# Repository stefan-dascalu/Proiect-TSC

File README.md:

Dascalu Stefan-Nicolae 331CA
# Proiect-TSC
## Implementare:

- **Implementarea Schemei Electrice:**
  - Am implementat schema electrica exact conform modelului primit.
  - Am efectuat o **verificare a regulilor electrice (ERC)**; desi am intampinat cateva avertismente, le-am revizuit si considerat necritice.

- **Designul PCB:**
  - Dupa finalizarea schemei, am incarcat designul in mediul PCB.
  - Toate componentele au fost amplasate pe **TOP layer** conform ghidurilor de layout.
  - Pentru a asigura **proper grounding** si **signal integrity**, am creat un **GND plane** atat pe TOP layer, cat si pe BOTTOM layer.
  - Am verificat toate constrangerile de design, iar rutarea a fost finalizata cu o rata de succes de 99,6%.
  - In timpul designului PCB, am intampinat si rezolvat erori de tip "airwire unrouted".

- **Fisiere de Productie:**
  - Am generat fisierele **Gerber**, **Pick and Place** si **BOM**.

- **Modelul 3D:**
  - Modelul 3D al dispozitivului a fost implementat.

## Imagine 3D

## Diagrama bloc a proiectului:

## Descriere Hardware si Asignarea Pinilor pe ESP32-C6

- **ESP32-C6-WROOM-1-N8 (Microcontroler Principal)**
  - Microcontrolerul ofera suport pentru WiFi 6, Bluetooth 5 LE si dispune de un nucleu RISC-V ce functioneaza pana la 160 MHz.
  - Interfetele disponibile includ SPI, I2C, UART si GPIO, fiind baza pentru conectarea celorlalte module.

- **BME688 (Senzor Ambiental)**
  - Maseaza temperatura, umiditatea, presiunea atmosferica si calitatea aerului.
  - Interfata: I2C
  - Pini utilizati: SDA -> IO21, SCL -> IO22
  - Alegerea acestor pini se face pentru a beneficia de o comunicatie I2C rapida si fiabila.

- **DS3231SN (Real-Time Clock)**
  - Asigura cronometrare de inalta precizie, chiar si in lipsa alimentarii principale.
  - Interfata: I2C (se partajeaza cu BME688)
  - Pini utilizati: SCL -> IO22, SDA -> IO21, INT_RTC -> IO8, 32KHZ -> IO1, RTC_RST -> IO18
  - Acesti pini asigura functii suplimentare de intrerupere si reset pentru modulul RTC.

- **Afisaj E-Ink (7.5 inch)**
  - Afisajul ofera o rezolutie de 800 x 480 pixeli si functioneaza prin interfata SPI.
  - Pini utilizati: EPD_CS -> IO10, EPD_DC -> IO5, EPD_RST -> IO23, EPD_BUSY -> IO3 (EPD_BUSY este partajat cu MISO)
  - Linile MOSI si SCK sunt partajate cu modulul SD, permitand optimizarea numarului de pini utilizati.

- **Modul SD Card**
  - Permite stocarea locala a datelor, cum ar fi e-bookurile sau firmware-ul.
  - Interfata: SPI
  - Pini utilizati: SS_SD -> IO4, MOSI -> IO7, MISO -> IO2, SCK -> IO6
  - Aceste asignari asigura sincronizarea corecta a datelor pe interfata SPI.

- **Memorie Externa Flash (W25Q512JVEIQ, 64MB)**
  - Memoria flash externa este utilizata pentru stocarea firmware-ului si a datelor importante.
  - Interfata: SPI
  - Pini utilizati: FLASH_CS -> IO12 (MOSI, MISO si SCK sunt partajate cu modulul SD)
  
- **Interfata USB/SD**
  - Asigura alimentarea si transferul de date prin USB.
  - Pini utilizati: USB_D+ -> IO13, USB_D- -> IO12

- **Butoane Boot si Reset**
  - Permit accesul la modul boot si efectuarea unui reset hardware.
  - Pini utilizati: IO/BOOT -> IO9, RESET -> un pin dedicat (conform schemei)

- **Sistem de Alimentare si Management**
  - Bateria Li-Po (3.7V, 2500mAh) alimenteaza sistemul.
  - Controlerul de incarcare MCP73831 gestioneaza incarcarea prin USB-C.
  - Monitorizarea bateriei se realizeaza cu MAX17048, care comunica prin I2C (reutilizand SDA/IO21 si SCL/IO22).
  - Regulatorul LDO XC6220A331MR-G furnizeaza 3.3V stabile pentru toate modulele.
  
- **Conector USB-C**
  - Principalul conector pentru alimentare si transfer de date, protejat de circuit ESD.

- **Conector Qwiic/Stemma QT**
  - Permite extinderea usoara a sistemului cu module suplimentare I2C.
  - Utilizeaza acelasi bus I2C (SDA -> IO21, SCL -> IO22) ca si senzorii si modulul RTC.

## BOM:
| Component                                               | Link             |
|---------------------------------------------------------|------------------|
| ADAFRUIT_LEDCHIP-LED0603                                  | [Click here](https://www.snapeda.com/parts/KP-1608SURCK/Kingbright/view-part/?ref=search&t=LED%200603)   |
| SJ                                                      | [Click here](https://grabcad.com/library/solder-jumpers-1)   |
| 112ATAARR03                       | [Click here](https://www.snapeda.com/parts/112A-TAAR-R03/Attend/view-part/)   |
| RCL_CPOL-EUCT3528                                       | [Click here](https://grabcad.com/library/tantalum-smd-capacitor-type-b-3528-1)   |
| BUTTON_CUSYOMV1                                         | [Click here](https://www.snapeda.com/search/?q=EVQP7L01P&search-type=parts)   |
| DS3231SN#                                              | [Click here](https://www.snapeda.com/parts/DS3231SN%23/Analog%20Devices/view-part/?ref=search&t=DS3231SN%23)   |
| ESP32-C6-WROOM-1-N8                                     | [Click here](https://www.snapeda.com/parts/ESP32-C6-WROOM-1-N8/Espressif%20Systems/view-part/?ref=search&t=ESP32-C6-WROOM-1-N8)   |
| 744043680                                 | [Click here](https://eu.mouser.com/ProductDetail/Wurth-Elektronik/744043680?qs=PGXP4M47uW6VkZq%252BkzjrHA%3D%3D)   |
| BD5229G-TR                                  | [Click here](https://www.snapeda.com/parts/BD5229G-TR/Rohm/view-part/?ref=search&t=BD5229G-TR)   |
| ESP32_WROVER_BME680_BME680                               | [Click here](https://www.snapeda.com/parts/BME680/Bosch%20Sensortec/view-part/?ref=search&t=bme680)   |
| ESP32_WROVER_EAGLE-LTSPICE_R                              | [Click here](https://componentsearchengine.com/part-view/R0402%201%25%20100%20K%20(RC0402FR-07100KL)/YAGEO)   |
| ESP32_WROVER_SPARKFUN-DISCRETESEMI_MOSFET_PCH                                | [Click here](https://componentsearchengine.com/part-view/DMG2305UX-7/Diodes%20Incorporated)   |
| ESP32_WROVER_SPARKFUN-IC-POWER_MCP73831                              | [Click here](https://componentsearchengine.com/part-view/MCP73831T-2ACI%2FOT/Microchip)   |
| FH34SRJ-24S-0.5SH_99_                                 | [Click here](https://componentsearchengine.com/part-view/FH34SRJ-24S-0.5SH(99)/Hirose)   |
| TP                                 | - |
| SI1308EDL-T1-GE3                                  | [Click here](https://www.snapeda.com/parts/SI1308EDL-T1-GE3/Vishay/view-part/)   |
| ESP32_WROVER_AVX---SD0805S020S1R0_AVX_SD0805S020S1R0_0_0  | [Click here](https://componentsearchengine.com/part-view/SD0805S020S1R0/Kyocera%20AVX)   |
| CPH3225A                                               | [Click here](https://www.snapeda.com/parts/CPH3225A/Seiko/view-part/)   |
| MAX17048G+T10                                          | [Click here](https://www.snapeda.com/parts/MAX17048G+T10/Analog%20Devices/view-part/)   |
| MBR0530                                               | [Click here](https://www.snapeda.com/parts/MBR0530/Onsemi/view-part/)   |
| PGB1010603MR                                           | [Click here](https://www.snapeda.com/parts/PGB1010603MR/Littelfuse/view-part/)   |
| QWIIC_RIGHT_ANGLE (QWIIC_CONNECTORJS-1MM)               | [Click here](https://www.snapeda.com/parts/PRT-14417/SparkFun/view-part/)   |
| SAMACSYS_PARTS_USB4110-GF-A                              | [Click here](https://www.snapeda.com/parts/USB4110-GF-A./Global%20Connector%20Technology/view-part/)   |
| USBLC6-2SC6Y                                           | [Click here](https://www.snapeda.com/parts/USBLC6-2SC6Y/STMicroelectronics/view-part/?ref=dk&t=USBLC6-2SC6Y&con_ref=None)   |
| W25Q512JVEIQ                                           | [Click here](https://www.snapeda.com/parts/W25Q512JVEIQ/Winbond%20Electronics/view-part/?ref=search&t=W25Q512JVEIQ)   |
| XC6220A331MR-G                                         | [Click here](https://ro.mouser.com/ProductDetail/Torex-Semiconductor/XC6220A331MR-G?qs=AsjdqWjXhJ8ZSWznL1J0gg%3D%3D&utm_source=octopart&utm_medium=aggregator&utm_campaign=865-XC6220A331MR-G&utm_content=Torex%20Semiconductor)   |

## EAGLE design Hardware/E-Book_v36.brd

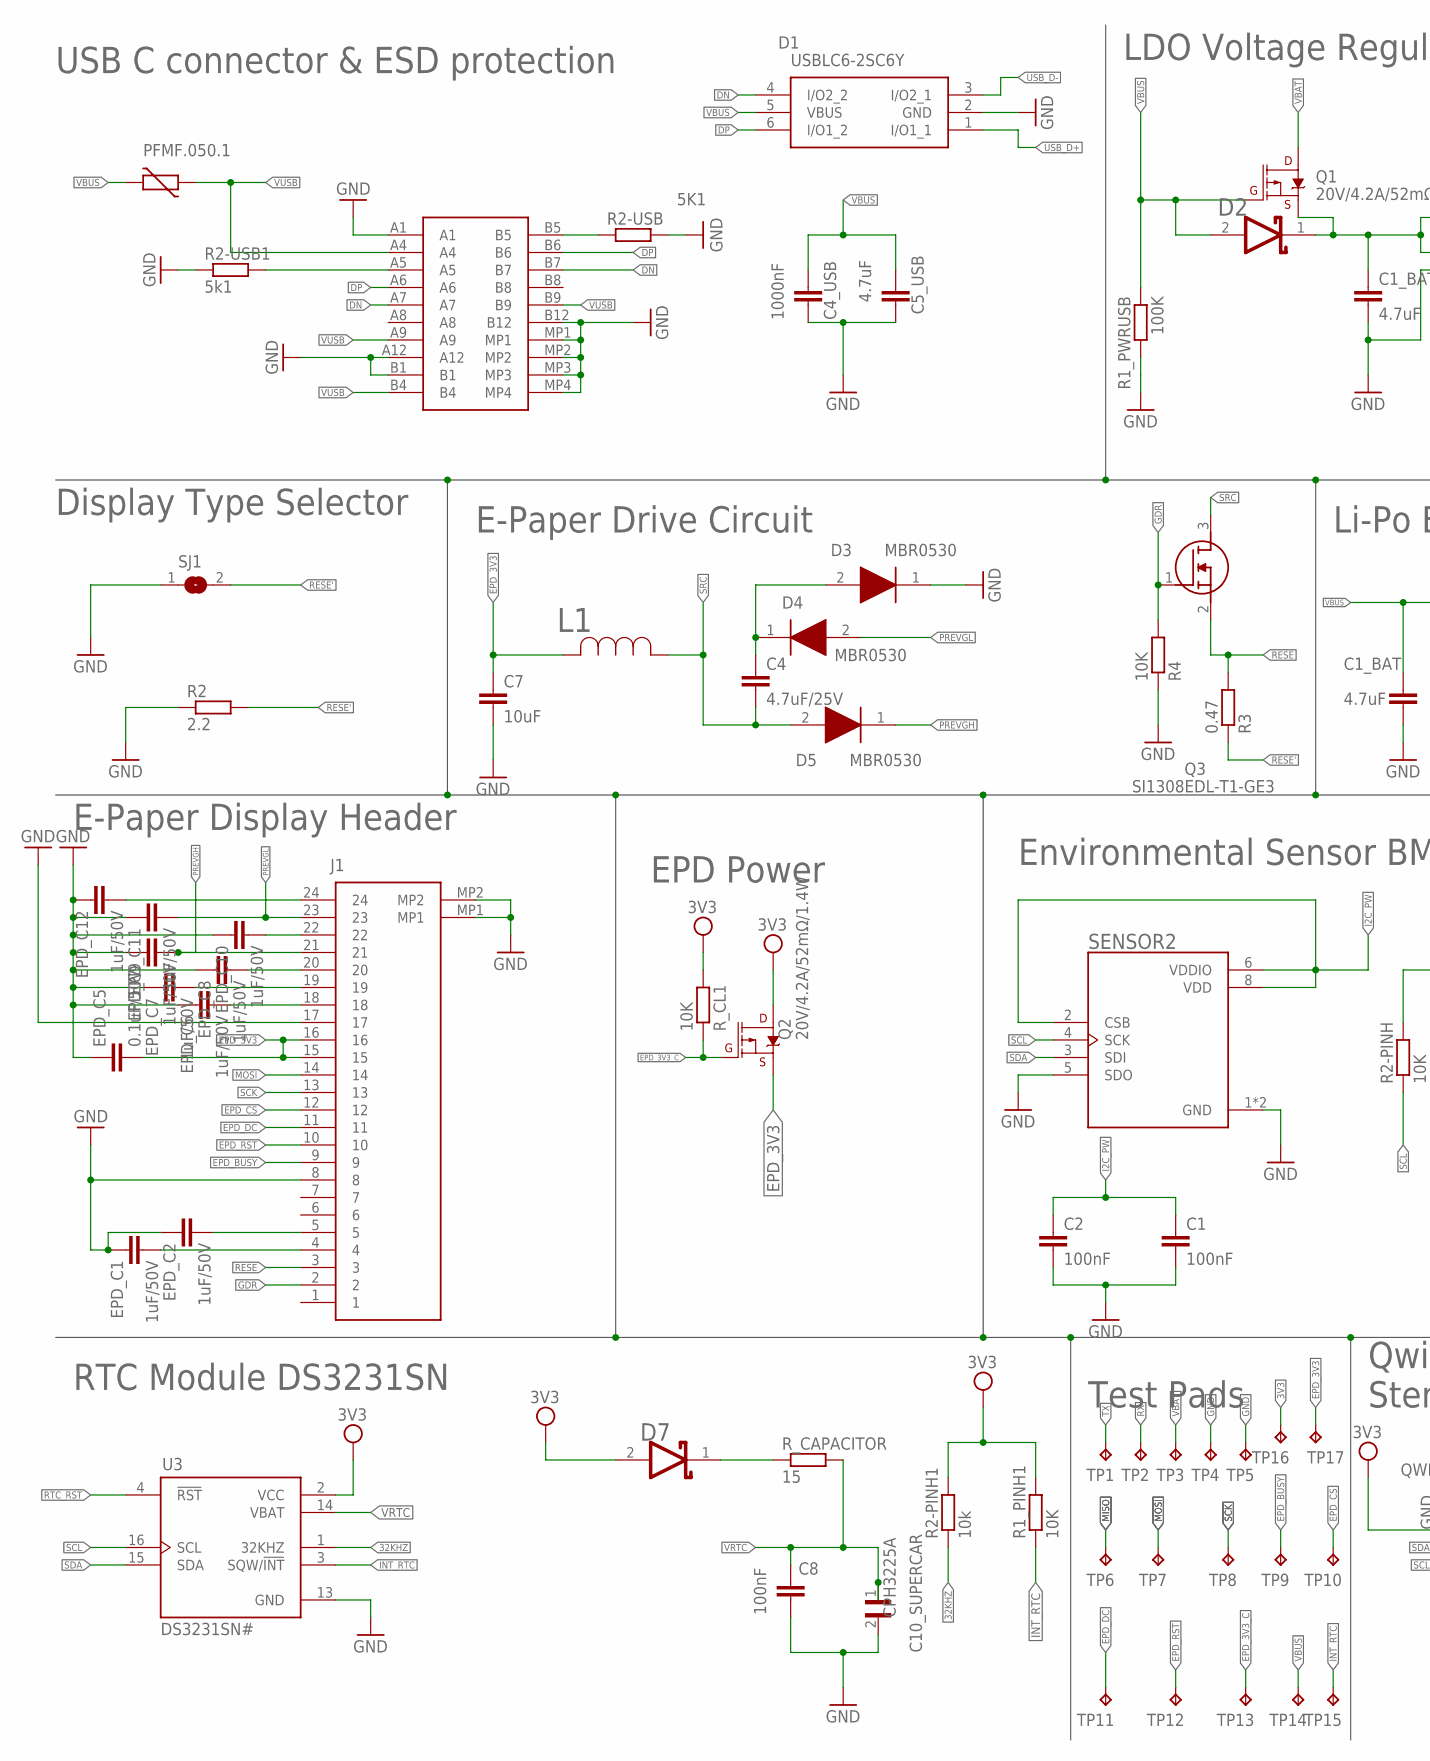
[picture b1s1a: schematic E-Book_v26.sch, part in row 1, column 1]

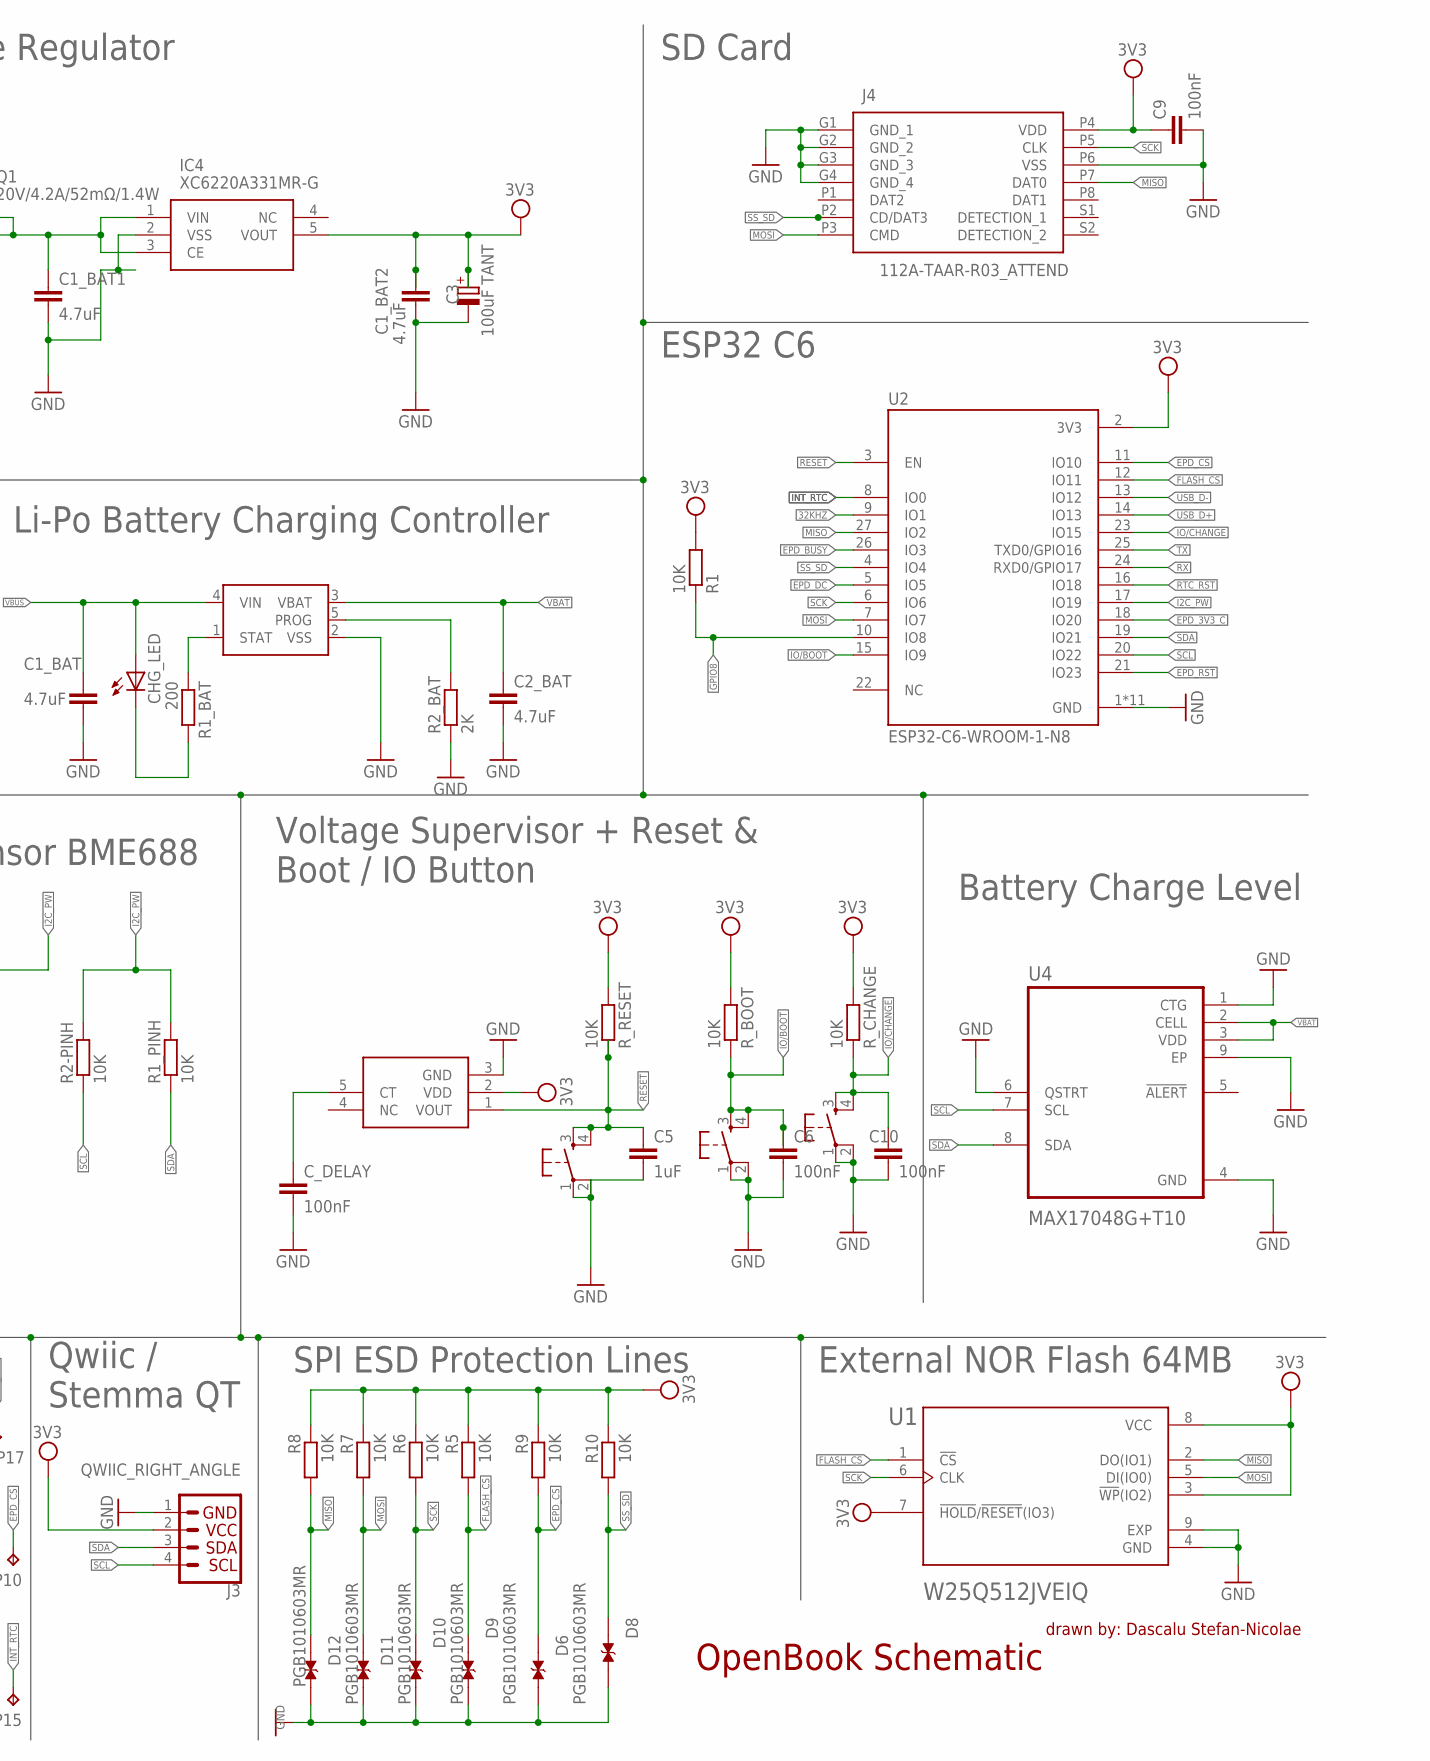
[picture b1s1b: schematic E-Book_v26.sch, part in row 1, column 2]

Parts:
C1, C2, C6, C8, C9, C10: 100nF; ESP32_WROVER_EAGLE-LTSPICE_C0402
C1_BAT, C2_BAT: 4.7uF; ESP32_WROVER_EAGLE-LTSPICE_C0402
C1_BAT1, C1_BAT2, C5_USB: 4.7uF; EAGLE-LTSPICE_C0402
C3: 100uF TANT; RCL_CT3528
C4: 4.7uF/25V; ESP32_WROVER_EAGLE-LTSPICE_C0402
C4_USB: 1000nF; EAGLE-LTSPICE_C0402
C5: 1uF; ESP32_WROVER_EAGLE-LTSPICE_C0402
C7: 10uF; ESP32_WROVER_EAGLE-LTSPICE_C0402
C10_SUPERCAR: CPH3225A; CAPCP3225X100N
CHG_LED: ADAFRUIT_LEDCHIP-LED0603; ADAFRUIT_CHIP-LED0603
C_DELAY: 100nF; ESP32_WROVER_EAGLE-LTSPICE_C0402
D1: USBLC6-2SC6Y; SOT95P280X145-6N
D2, D7: ESP32_WROVER_AVX---SD0805S020S1R0_AVX_SD0805S020S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; ESP32_WROVER_AVX---SD0805S020S1R0_AVX_SD0805S020S1R0_0
D3, D4, D5: MBR0530; SOD3716X135N
D6, D8, D9, D10, D11, D12: PGB1010603MR; DIOC1608X36N
EPD_C1, EPD_C2, EPD_C6, EPD_C7, EPD_C8, EPD_C9, EPD_C10, EPD_C11, EPD_C12: 1uF/50V; ESP32_WROVER_EAGLE-LTSPICE_C0402
EPD_C5: 0.1uF/50V; ESP32_WROVER_EAGLE-LTSPICE_C0402
IC1: BD5229G-TR; SOT95P280X125-5N
IC4: XC6220A331MR-G; SOT95P280X120-5N
J1: FH34SRJ-24S-0.5SH_99_; FH34SRJ24S05SH99
J2: SAMACSYS_PARTS_USB4110-GF-A; SAMACSYS_PARTS_USB4110GFA
J3: QWIIC_RIGHT_ANGLE; JST04_1MM_RA
J4: 112A-TAAR-R03_ATTEND; 112ATAARR03ATTEND
L1: 744043680IND_4828-WE-TPC_WRE; IND_4828-WE-TPC_WRE
MCP73831: ESP32_WROVER_SPARKFUN-IC-POWER_MCP73831; ESP32_WROVER_SPARKFUN-IC-POWER_SOT23-5
PFMF.050.1: ESP32C6_VARISTORCN1812; ESP32C6_VARISTOR_CT/CN1812
Q1, Q2: 20V/4.2A/52mΩ/1.4W; ESP32_WROVER_SPARKFUN-DISCRETESEMI_SOT23-3
Q3: SI1308EDL-T1-GE3; SOT65P210X110-3N
R1, R1_PINH, R1_PINH1, R2-PINH, R4, R5, R6, R7, R8, R9, R10: 10K; ESP32_WROVER_EAGLE-LTSPICE_R0402
R1_BAT: 200; ESP32_WROVER_EAGLE-LTSPICE_R0402
R1_PWRUSB: 100K; ESP32_WROVER_EAGLE-LTSPICE_R0402
R2: 2.2; ESP32_WROVER_EAGLE-LTSPICE_R0402
R2-PINH1: 10k; ESP32_WROVER_EAGLE-LTSPICE_R0402
R2-USB: 5K1; ESP32_WROVER_EAGLE-LTSPICE_R0402
R2-USB1: 5k1; ESP32_WROVER_EAGLE-LTSPICE_R0402
R2_BAT: 2K; ESP32_WROVER_EAGLE-LTSPICE_R0402
R3: 0.47; ESP32_WROVER_EAGLE-LTSPICE_R0402
RESET_BUTTON: BUTTON_CUSYOMV1; MYBUTTON
R_BOOT: 10K; ESP32_WROVER_EAGLE-LTSPICE_R0402
R_CAPACITOR: 15; ESP32_WROVER_EAGLE-LTSPICE_R0402
R_CHANGE: 10K; ESP32_WROVER_EAGLE-LTSPICE_R0402
R_CL1: 10K; ESP32_WROVER_EAGLE-LTSPICE_R0402
R_RESET: 10K; ESP32_WROVER_EAGLE-LTSPICE_R0402
SENSOR2: ESP32_WROVER_BME680_BME680; ESP32_WROVER_BME680_PSON80P300X300X100-8N
SJ1: SJ
TP1, TP2, TP3, TP4, TP5, TP6, TP7, TP8, TP9, TP10, TP11, TP12, TP13, TP14, TP15, TP16, TP17: TPTP20R; TP20R
U1: W25Q512JVEIQ; SON127P600X800X80-9N
U2: ESP32-C6-WROOM-1-N8; XCVR_ESP32-C6-WROOM-1-N8
U3: DS3231SN#; SOIC127P1032X265-16N
U4: MAX17048G+T10; SON50P200X200X80-9N
U$1, U$3: BUTTON_CUSYOMV1; MYBUTTON

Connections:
3V3: C1_BAT2.1, C3.+, C9.1, D7.2 (ANODE), IC1.2 (VDD), IC4.5 (VOUT), J3.2, J4.P4 (VDD), Q2.3 (D), R1.2, R1_PINH1.2, R2-PINH1.2, R5.1, R6.1, R7.1, R8.1, R9.1, R10.1, R_BOOT.2, R_CHANGE.2, R_CL1.2, R_RESET.2, TP16.TP, U1.3 (!WP!(IO2)), U1.7 (!HOLD!/!RESET!(IO3)), U1.8 (VCC), U2.2 (3V3), U3.2 (VCC)
32KHZ: R2-PINH1.1, U2.9 (IO1), U3.1 (32KHZ)
DN: D1.4 (I/O2_2), J2.A7, J2.B7
DP: D1.6 (I/O1_2), J2.A6, J2.B6
EPD_3V3: C7.1, EPD_C5.2, J1.15, J1.16, L1.2, Q2.2 (S), TP17.TP
EPD_3V3_C: Q2.1 (G), R_CL1.1, TP13.TP, U2.18 (IO20)
EPD_BUSY: J1.9, TP9.TP, U2.26 (IO3)
EPD_CS: D6.1, J1.12, R9.2, TP10.TP, U2.11 (IO10)
EPD_DC: J1.11, TP11.TP, U2.5 (IO5)
EPD_RST: J1.10, TP12.TP, U2.21 (IO23)
FLASH_CS: D9.1, R5.2, U1.1 (!CS), U2.12 (IO11)
GDR: J1.2, Q3.1 (G), R4.2
GND: C1.2, C1_BAT.2, C1_BAT1.2, C1_BAT2.2, C2.2, C2_BAT.2, C3.-, C4_USB.2, C5.2, C5_USB.2, C6.2, C7.2, C8.2, C9.2, C10.2, C10_SUPERCAR.2, C_DELAY.2, D1.2 (GND), D3.1 (K), D6.2, D8.2, D9.2, D10.2, D11.2, D12.2, EPD_C1.1, EPD_C2.1, EPD_C5.1, EPD_C6.1, EPD_C7.1, EPD_C8.1, EPD_C9.1, EPD_C10.1, EPD_C11.1, EPD_C12.1, IC1.3 (GND), IC4.2 (VSS), J1.8, J1.17, J1.MP1, J1.MP2, J2.A1, J2.A12, J2.B1, J2.B12, J2.MP1, J2.MP2, J2.MP3, J2.MP4, J3.1, J4.G1 (GND_1), J4.G2 (GND_2), J4.G3 (GND_3), J4.G4 (GND_4), J4.P6 (VSS), MCP73831.2 (VSS), R1_PWRUSB.2, R2.1, R2-USB.2, R2-USB1.1, R2_BAT.1, R4.1, RESET_BUTTON.1, RESET_BUTTON.2, SENSOR2.1 (GND), SENSOR2.5 (SDO), SENSOR2.7 (GND), SJ1.1, TP4.TP, TP5.TP, U1.4 (GND), U1.9 (EXP), U2.1 (GND), U2.28 (GND), U2.29_1 (GND), U2.29_2 (GND), U2.29_3 (GND), U2.29_4 (GND), U2.29_5 (GND), U2.29_6 (GND), U2.29_7 (GND), U2.29_8 (GND), U2.29_9 (GND), U3.13 (GND), U4.1 (CTG), U4.4 (GND), U4.6 (QSTRT), U4.9 (EP), U$1.1, U$1.2, U$3.1, U$3.2
GPIO8: R1.1, U2.10 (IO8)
I2C_PW: C1.1, C2.1, R1_PINH.2, R2-PINH.2, SENSOR2.2 (CSB), SENSOR2.6 (VDDIO), SENSOR2.8 (VDD), U2.17 (IO19)
INT_RTC: R1_PINH1.1, TP15.TP, U2.8 (IO0), U3.3 (SQW/!INT)
IO/BOOT: C6.1, R_BOOT.1, U2.15 (IO9), U$3.3, U$3.4
IO/CHANGE: C10.1, R_CHANGE.1, U2.23 (IO15), U$1.3, U$1.4
MISO: D12.1, J4.P7 (DAT0), R8.2, TP6.TP, U1.2 (DO(IO1)), U2.27 (IO2)
MOSI: D11.1, J1.14, J4.P3 (CMD), R7.2, TP7.TP, U1.5 (DI(IO0)), U2.7 (IO7)
unnamed: J2.B5, R2-USB.1
unnamed: J2.A5, R2-USB1.2
unnamed: CHG_LED.C, R1_BAT.2
unnamed: EPD_C1.2, J1.4
unnamed: MCP73831.5 (PROG), R2_BAT.2
unnamed: EPD_C2.2, J1.5
unnamed: MCP73831.1 (STAT), R1_BAT.1
unnamed: EPD_C6.2, J1.18
unnamed: EPD_C7.2, J1.19
unnamed: EPD_C8.2, J1.20
unnamed: EPD_C10.2, J1.22
unnamed: EPD_C12.2, J1.24
unnamed: C_DELAY.1, IC1.5 (CT)
unnamed: C1_BAT1.1, D2.1 (CATHODE), IC4.1 (VIN), IC4.3 (CE), Q1.2 (S)
unnamed: C4.1, D3.2 (A), D4.1 (K)
unnamed: D7.1 (CATHODE), R_CAPACITOR.1
PREVGH: D5.1 (K), EPD_C9.2, J1.21
PREVGL: D4.2 (A), EPD_C11.2, J1.23
RESE: J1.3, Q3.2 (S), R3.2
RESE': R2.2, R3.1, SJ1.2
RESET: C5.1, IC1.1 (VOUT), RESET_BUTTON.3, RESET_BUTTON.4, R_RESET.1, U2.3 (EN)
RTC_RST: U2.16 (IO18), U3.4 (!RST)
RX: TP2.TP, U2.24 (RXD0/GPIO17)
SCK: D10.1, J1.13, J4.P5 (CLK), R6.2, TP8.TP, U1.6 (CLK), U2.6 (IO6)
SCL: J3.4, R2-PINH.1, SENSOR2.4 (SCK), U2.20 (IO22), U3.16 (SCL), U4.7 (SCL)
SDA: J3.3, R1_PINH.1, SENSOR2.3 (SDI), U2.19 (IO21), U3.15 (SDA), U4.8 (SDA)
SRC: C4.2, D5.2 (A), L1.1, Q3.3 (D)
SS_SD: D8.1, J4.P2 (CD/DAT3), R10.2, U2.4 (IO4)
TX: TP1.TP, U2.25 (TXD0/GPIO16)
USB_D+: D1.1 (I/O1_1), U2.14 (IO13)
USB_D-: D1.3 (I/O2_1), U2.13 (IO12)
VBAT: C2_BAT.1, MCP73831.3 (VBAT), Q1.3 (D), TP3.TP, U4.2 (CELL), U4.3 (VDD)
VBUS: C1_BAT.1, C4_USB.1, C5_USB.1, CHG_LED.A, D1.5 (VBUS), D2.2 (ANODE), MCP73831.4 (VIN), PFMF.050.1.2, Q1.1 (G), R1_PWRUSB.1, TP14.TP
VRTC: C8.1, C10_SUPERCAR.1, R_CAPACITOR.2, U3.14 (VBAT)
VUSB: J2.A4, J2.A9, J2.B4, J2.B9, PFMF.050.1.1

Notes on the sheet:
USB C connector & ESD protection
Display Type Selector
Test Pads
Qwiic / Stemma QT
External NOR Flash 64MB
drawn by: Dascalu Stefan-Nicolae
Battery Charge Level
OpenBook Schematic
EPD Power
Environmental Sensor BME688
SD Card
ESP32 C6
Li-Po Battery Charging Controller
E-Paper Display Header
SPI ESD Protection Lines
LDO Voltage Regulator
Voltage Supervisor + Reset & Boot / IO Button
E-Paper Drive Circuit
RTC Module DS3231SN

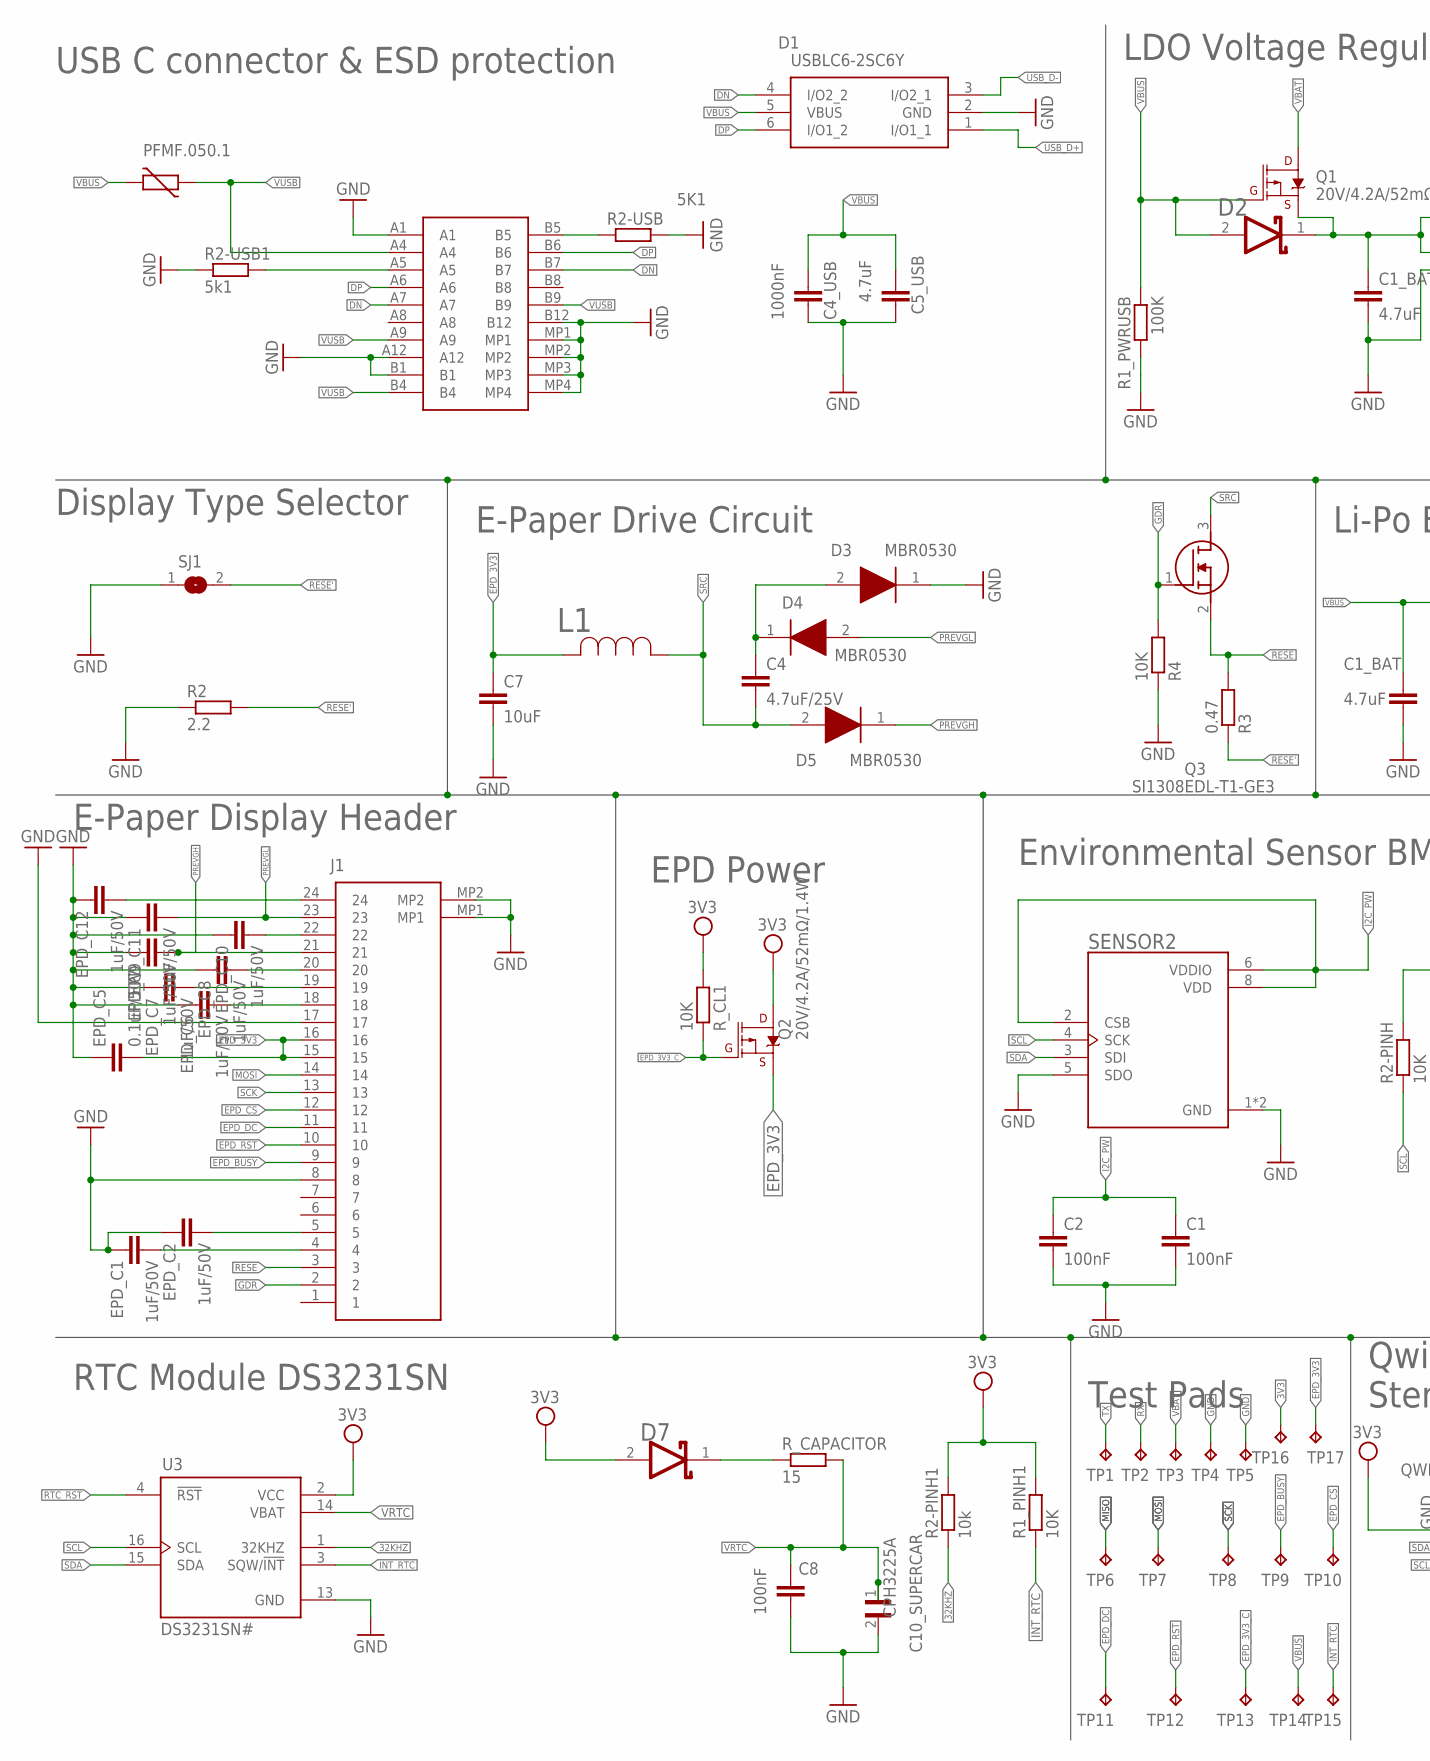
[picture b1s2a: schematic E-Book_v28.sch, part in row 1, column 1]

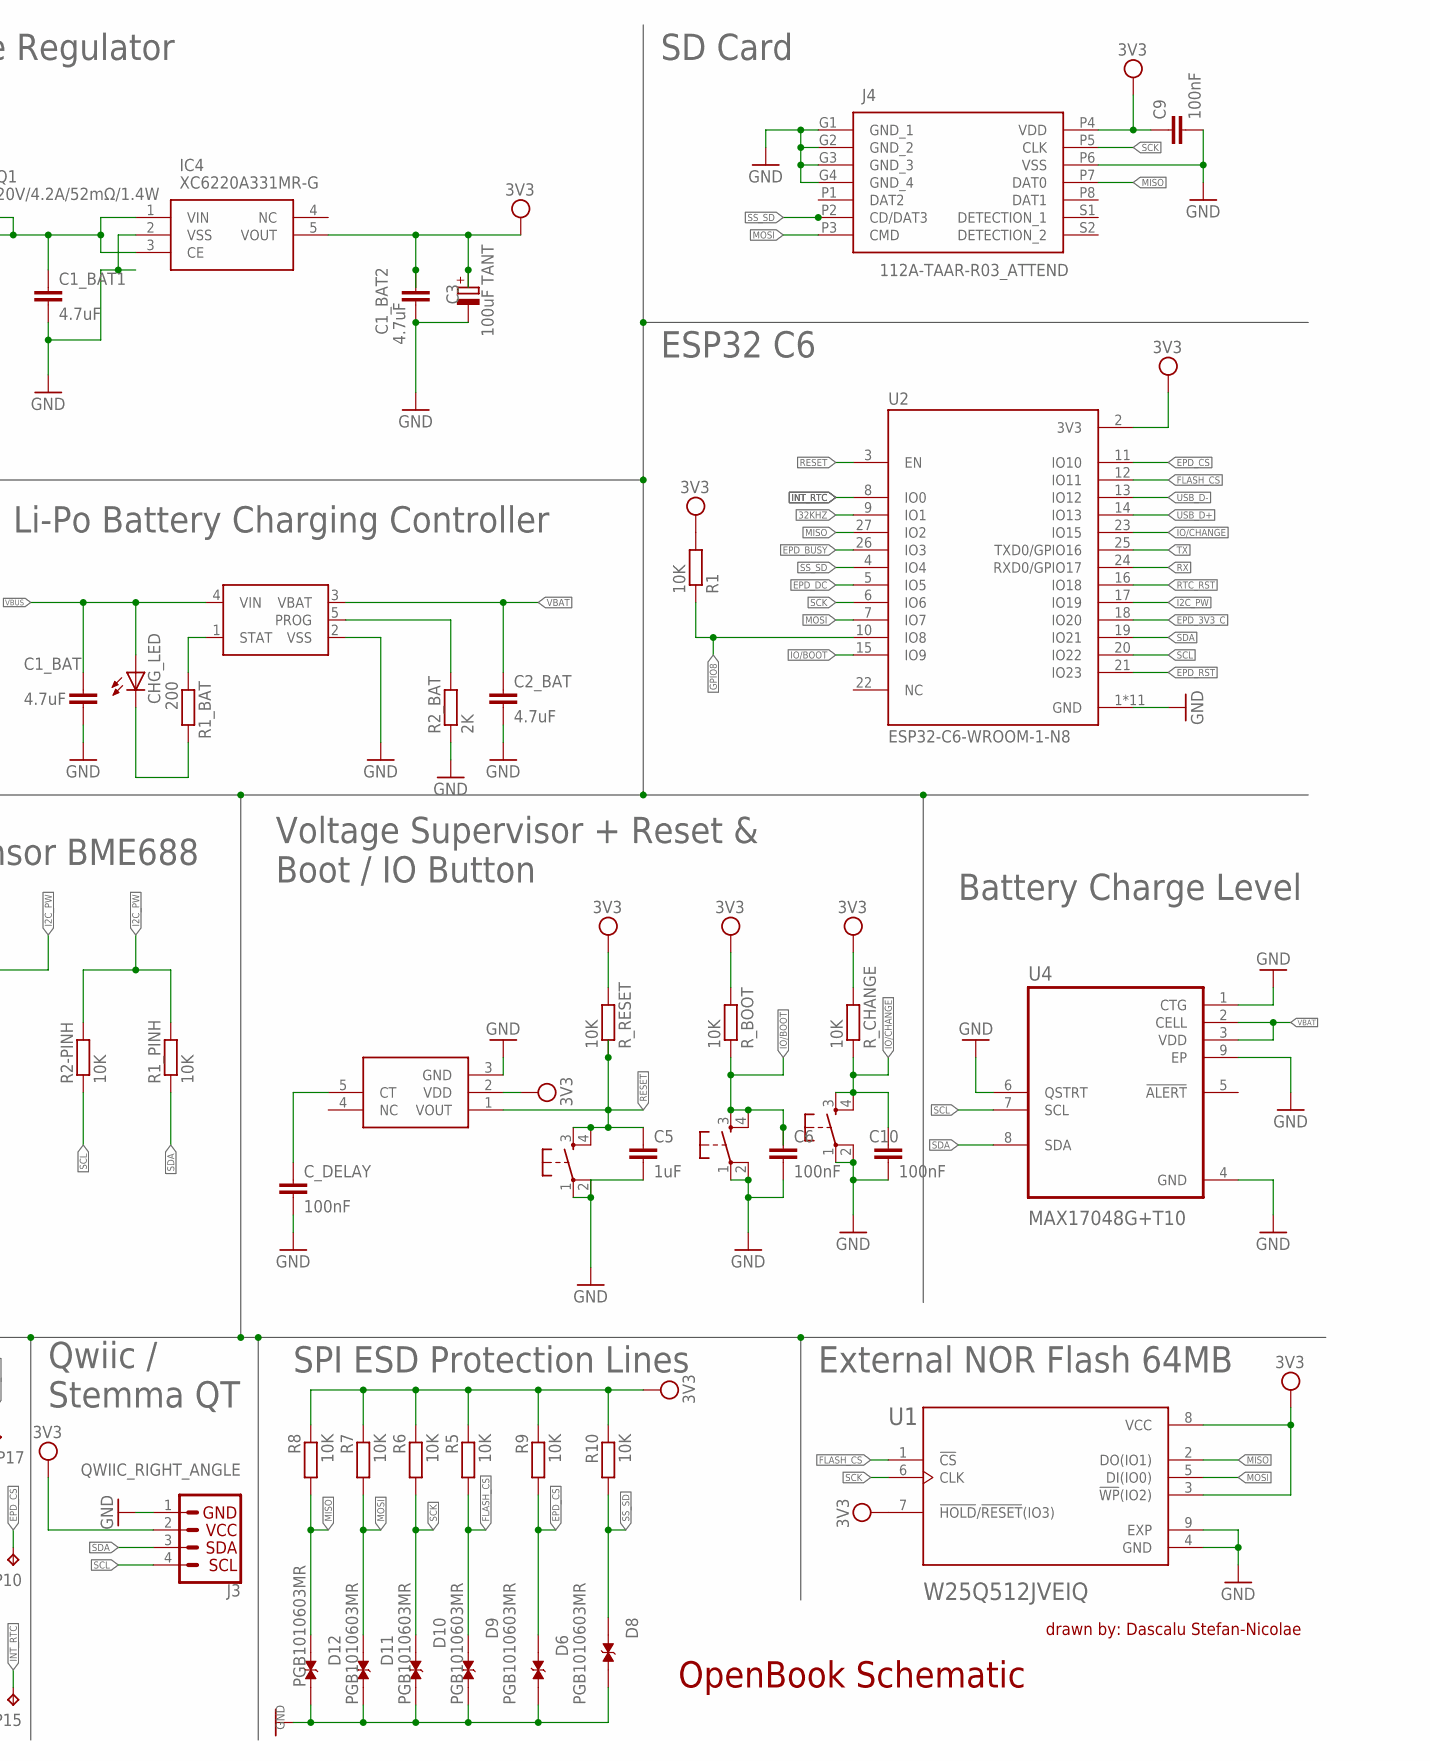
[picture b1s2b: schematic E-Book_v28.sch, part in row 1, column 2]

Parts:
C1, C2, C6, C8, C9, C10: 100nF; ESP32_WROVER_EAGLE-LTSPICE_C0402
C1_BAT, C2_BAT: 4.7uF; ESP32_WROVER_EAGLE-LTSPICE_C0402
C1_BAT1, C1_BAT2, C5_USB: 4.7uF; EAGLE-LTSPICE_C0402
C3: 100uF TANT; RCL_CT3528
C4: 4.7uF/25V; ESP32_WROVER_EAGLE-LTSPICE_C0402
C4_USB: 1000nF; EAGLE-LTSPICE_C0402
C5: 1uF; ESP32_WROVER_EAGLE-LTSPICE_C0402
C7: 10uF; ESP32_WROVER_EAGLE-LTSPICE_C0402
C10_SUPERCAR: CPH3225A; CAPCP3225X100N
CHG_LED: ADAFRUIT_LEDCHIP-LED0603; ADAFRUIT_CHIP-LED0603
C_DELAY: 100nF; ESP32_WROVER_EAGLE-LTSPICE_C0402
D1: USBLC6-2SC6Y; SOT95P280X145-6N
D2, D7: ESP32_WROVER_AVX---SD0805S020S1R0_AVX_SD0805S020S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; ESP32_WROVER_AVX---SD0805S020S1R0_AVX_SD0805S020S1R0_0
D3, D4, D5: MBR0530; SOD3716X135N
D6, D8, D9, D10, D11, D12: PGB1010603MR; DIOC1608X36N
EPD_C1, EPD_C2, EPD_C6, EPD_C7, EPD_C8, EPD_C9, EPD_C10, EPD_C11, EPD_C12: 1uF/50V; ESP32_WROVER_EAGLE-LTSPICE_C0402
EPD_C5: 0.1uF/50V; ESP32_WROVER_EAGLE-LTSPICE_C0402
IC1: BD5229G-TR; SOT95P280X125-5N
IC4: XC6220A331MR-G; SOT95P280X120-5N
J1: FH34SRJ-24S-0.5SH_99_; FH34SRJ24S05SH99
J2: SAMACSYS_PARTS_USB4110-GF-A; SAMACSYS_PARTS_USB4110GFA
J3: QWIIC_RIGHT_ANGLE; JST04_1MM_RA
J4: 112A-TAAR-R03_ATTEND; 112ATAARR03ATTEND
L1: 744043680IND_4828-WE-TPC_WRE; IND_4828-WE-TPC_WRE
MCP73831: ESP32_WROVER_SPARKFUN-IC-POWER_MCP73831; ESP32_WROVER_SPARKFUN-IC-POWER_SOT23-5
PFMF.050.1: ESP32C6_VARISTORCN1812; ESP32C6_VARISTOR_CT/CN1812
Q1, Q2: 20V/4.2A/52mΩ/1.4W; ESP32_WROVER_SPARKFUN-DISCRETESEMI_SOT23-3
Q3: SI1308EDL-T1-GE3; SOT65P210X110-3N
R1, R1_PINH, R1_PINH1, R2-PINH, R4, R5, R6, R7, R8, R9, R10: 10K; ESP32_WROVER_EAGLE-LTSPICE_R0402
R1_BAT: 200; ESP32_WROVER_EAGLE-LTSPICE_R0402
R1_PWRUSB: 100K; ESP32_WROVER_EAGLE-LTSPICE_R0402
R2: 2.2; ESP32_WROVER_EAGLE-LTSPICE_R0402
R2-PINH1: 10k; ESP32_WROVER_EAGLE-LTSPICE_R0402
R2-USB: 5K1; ESP32_WROVER_EAGLE-LTSPICE_R0402
R2-USB1: 5k1; ESP32_WROVER_EAGLE-LTSPICE_R0402
R2_BAT: 2K; ESP32_WROVER_EAGLE-LTSPICE_R0402
R3: 0.47; ESP32_WROVER_EAGLE-LTSPICE_R0402
RESET_BUTTON: BUTTON_CUSYOMV1; MYBUTTON
R_BOOT: 10K; ESP32_WROVER_EAGLE-LTSPICE_R0402
R_CAPACITOR: 15; ESP32_WROVER_EAGLE-LTSPICE_R0402
R_CHANGE: 10K; ESP32_WROVER_EAGLE-LTSPICE_R0402
R_CL1: 10K; ESP32_WROVER_EAGLE-LTSPICE_R0402
R_RESET: 10K; ESP32_WROVER_EAGLE-LTSPICE_R0402
SENSOR2: ESP32_WROVER_BME680_BME680; ESP32_WROVER_BME680_PSON80P300X300X100-8N
SJ1: SJ
TP1, TP2, TP3, TP4, TP5, TP6, TP7, TP8, TP9, TP10, TP11, TP12, TP13, TP14, TP15, TP16, TP17: TPTP20R; TP20R
U1: W25Q512JVEIQ; SON127P600X800X80-9N
U2: ESP32-C6-WROOM-1-N8; XCVR_ESP32-C6-WROOM-1-N8
U3: DS3231SN#; SOIC127P1032X265-16N
U4: MAX17048G+T10; SON50P200X200X80-9N
U$1, U$3: BUTTON_CUSYOMV1; MYBUTTON

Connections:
3V3: C1_BAT2.1, C3.+, C9.1, D7.2 (ANODE), IC1.2 (VDD), IC4.5 (VOUT), J3.2, J4.P4 (VDD), Q2.3 (D), R1.2, R1_PINH1.2, R2-PINH1.2, R5.1, R6.1, R7.1, R8.1, R9.1, R10.1, R_BOOT.2, R_CHANGE.2, R_CL1.2, R_RESET.2, TP16.TP, U1.3 (!WP!(IO2)), U1.7 (!HOLD!/!RESET!(IO3)), U1.8 (VCC), U2.2 (3V3), U3.2 (VCC)
32KHZ: R2-PINH1.1, U2.9 (IO1), U3.1 (32KHZ)
DN: D1.4 (I/O2_2), J2.A7, J2.B7
DP: D1.6 (I/O1_2), J2.A6, J2.B6
EPD_3V3: C7.1, EPD_C5.2, J1.15, J1.16, L1.2, Q2.2 (S), TP17.TP
EPD_3V3_C: Q2.1 (G), R_CL1.1, TP13.TP, U2.18 (IO20)
EPD_BUSY: J1.9, TP9.TP, U2.26 (IO3)
EPD_CS: D6.1, J1.12, R9.2, TP10.TP, U2.11 (IO10)
EPD_DC: J1.11, TP11.TP, U2.5 (IO5)
EPD_RST: J1.10, TP12.TP, U2.21 (IO23)
FLASH_CS: D9.1, R5.2, U1.1 (!CS), U2.12 (IO11)
GDR: J1.2, Q3.1 (G), R4.2
GND: C1.2, C1_BAT.2, C1_BAT1.2, C1_BAT2.2, C2.2, C2_BAT.2, C3.-, C4_USB.2, C5.2, C5_USB.2, C6.2, C7.2, C8.2, C9.2, C10.2, C10_SUPERCAR.2, C_DELAY.2, D1.2 (GND), D3.1 (K), D6.2, D8.2, D9.2, D10.2, D11.2, D12.2, EPD_C1.1, EPD_C2.1, EPD_C5.1, EPD_C6.1, EPD_C7.1, EPD_C8.1, EPD_C9.1, EPD_C10.1, EPD_C11.1, EPD_C12.1, IC1.3 (GND), IC4.2 (VSS), J1.8, J1.17, J1.MP1, J1.MP2, J2.A1, J2.A12, J2.B1, J2.B12, J2.MP1, J2.MP2, J2.MP3, J2.MP4, J3.1, J4.G1 (GND_1), J4.G2 (GND_2), J4.G3 (GND_3), J4.G4 (GND_4), J4.P6 (VSS), MCP73831.2 (VSS), R1_PWRUSB.2, R2.1, R2-USB.2, R2-USB1.1, R2_BAT.1, R4.1, RESET_BUTTON.1, RESET_BUTTON.2, SENSOR2.1 (GND), SENSOR2.5 (SDO), SENSOR2.7 (GND), SJ1.1, TP4.TP, TP5.TP, U1.4 (GND), U1.9 (EXP), U2.1 (GND), U2.28 (GND), U2.29_1 (GND), U2.29_2 (GND), U2.29_3 (GND), U2.29_4 (GND), U2.29_5 (GND), U2.29_6 (GND), U2.29_7 (GND), U2.29_8 (GND), U2.29_9 (GND), U3.13 (GND), U4.1 (CTG), U4.4 (GND), U4.6 (QSTRT), U4.9 (EP), U$1.1, U$1.2, U$3.1, U$3.2
GPIO8: R1.1, U2.10 (IO8)
I2C_PW: C1.1, C2.1, R1_PINH.2, R2-PINH.2, SENSOR2.2 (CSB), SENSOR2.6 (VDDIO), SENSOR2.8 (VDD), U2.17 (IO19)
INT_RTC: R1_PINH1.1, TP15.TP, U2.8 (IO0), U3.3 (SQW/!INT)
IO/BOOT: C6.1, R_BOOT.1, U2.15 (IO9), U$3.3, U$3.4
IO/CHANGE: C10.1, R_CHANGE.1, U2.23 (IO15), U$1.3, U$1.4
MISO: D12.1, J4.P7 (DAT0), R8.2, TP6.TP, U1.2 (DO(IO1)), U2.27 (IO2)
MOSI: D11.1, J1.14, J4.P3 (CMD), R7.2, TP7.TP, U1.5 (DI(IO0)), U2.7 (IO7)
unnamed: J2.B5, R2-USB.1
unnamed: J2.A5, R2-USB1.2
unnamed: CHG_LED.C, R1_BAT.2
unnamed: EPD_C1.2, J1.4
unnamed: MCP73831.5 (PROG), R2_BAT.2
unnamed: EPD_C2.2, J1.5
unnamed: MCP73831.1 (STAT), R1_BAT.1
unnamed: EPD_C6.2, J1.18
unnamed: EPD_C7.2, J1.19
unnamed: EPD_C8.2, J1.20
unnamed: EPD_C10.2, J1.22
unnamed: EPD_C12.2, J1.24
unnamed: C_DELAY.1, IC1.5 (CT)
unnamed: C1_BAT1.1, D2.1 (CATHODE), IC4.1 (VIN), IC4.3 (CE), Q1.2 (S)
unnamed: C4.1, D3.2 (A), D4.1 (K)
unnamed: D7.1 (CATHODE), R_CAPACITOR.1
PREVGH: D5.1 (K), EPD_C9.2, J1.21
PREVGL: D4.2 (A), EPD_C11.2, J1.23
RESE: J1.3, Q3.2 (S), R3.2
RESE': R2.2, R3.1, SJ1.2
RESET: C5.1, IC1.1 (VOUT), RESET_BUTTON.3, RESET_BUTTON.4, R_RESET.1, U2.3 (EN)
RTC_RST: U2.16 (IO18), U3.4 (!RST)
RX: TP2.TP, U2.24 (RXD0/GPIO17)
SCK: D10.1, J1.13, J4.P5 (CLK), R6.2, TP8.TP, U1.6 (CLK), U2.6 (IO6)
SCL: J3.4, R2-PINH.1, SENSOR2.4 (SCK), U2.20 (IO22), U3.16 (SCL), U4.7 (SCL)
SDA: J3.3, R1_PINH.1, SENSOR2.3 (SDI), U2.19 (IO21), U3.15 (SDA), U4.8 (SDA)
SRC: C4.2, D5.2 (A), L1.1, Q3.3 (D)
SS_SD: D8.1, J4.P2 (CD/DAT3), R10.2, U2.4 (IO4)
TX: TP1.TP, U2.25 (TXD0/GPIO16)
USB_D+: D1.1 (I/O1_1), U2.14 (IO13)
USB_D-: D1.3 (I/O2_1), U2.13 (IO12)
VBAT: C2_BAT.1, MCP73831.3 (VBAT), Q1.3 (D), TP3.TP, U4.2 (CELL), U4.3 (VDD)
VBUS: C1_BAT.1, C4_USB.1, C5_USB.1, CHG_LED.A, D1.5 (VBUS), D2.2 (ANODE), MCP73831.4 (VIN), PFMF.050.1.2, Q1.1 (G), R1_PWRUSB.1, TP14.TP
VRTC: C8.1, C10_SUPERCAR.1, R_CAPACITOR.2, U3.14 (VBAT)
VUSB: J2.A4, J2.A9, J2.B4, J2.B9, PFMF.050.1.1

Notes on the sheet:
USB C connector & ESD protection
Display Type Selector
Test Pads
Qwiic / Stemma QT
External NOR Flash 64MB
drawn by: Dascalu Stefan-Nicolae
Battery Charge Level
OpenBook Schematic
EPD Power
Environmental Sensor BME688
SD Card
ESP32 C6
Li-Po Battery Charging Controller
E-Paper Display Header
SPI ESD Protection Lines
LDO Voltage Regulator
Voltage Supervisor + Reset & Boot / IO Button
E-Paper Drive Circuit
RTC Module DS3231SN

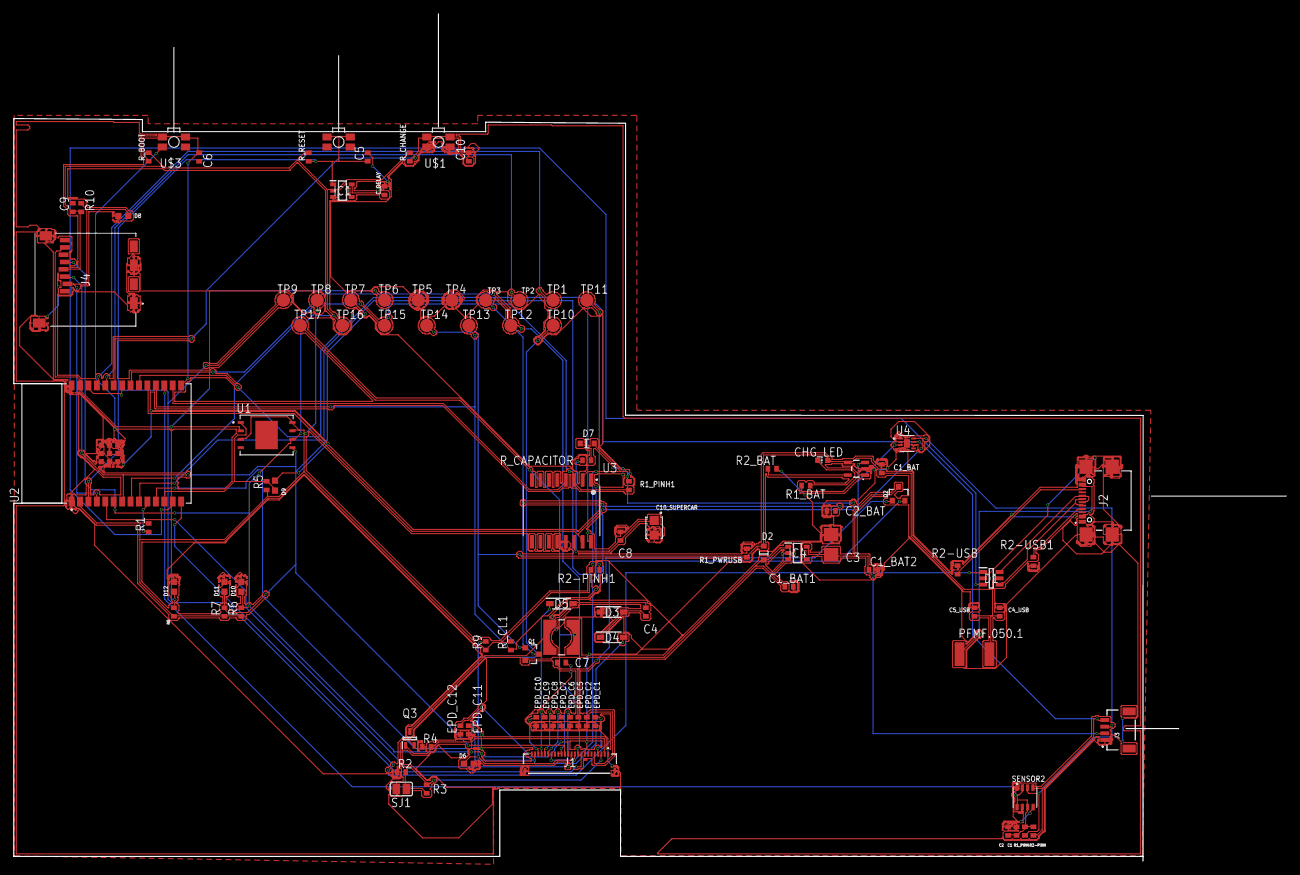
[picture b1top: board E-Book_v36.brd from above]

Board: 2 copper layers, 191.8 x 127.7 mm, 103 parts (0 on the bottom side), 55 nets.

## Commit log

2025-04-06 Create LICENSE
2025-04-06 Create dummy
2025-04-06 Rename E-Book v9.csv to BillofMaterials.csv
2025-04-06 Rename Unknown.jpeg to diagrama.jpeg
2025-04-10 Rename BillofMaterials.csv to BillofMaterials.bom

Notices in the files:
parts and their libraries:
DeskAssistant v19 v1: COPYRIGHT: Copyright (C) 2024 Ultra Librarian. All rights reserved.
